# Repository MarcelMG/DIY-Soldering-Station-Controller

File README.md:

# DIY-Soldering-Station-Controller
A soldering station controller compatible with [Weller RT active tips](https://www.weller-tools.com/professional/USA/us/Professional/Soldering+technology/Soldering+tips+_+nozzles/Soldering+tips/RT+Active+Tips)
The design is kept simple, with a rotary encoder with internal pushbutton to set the temperature and
a TM1637 4-digit 7-segment LED display. When the pushbutton is pressed for >3s, the current target temperature is stored as default value in the non-volatile EEPROM memory of the microcontroller. When the iron handle is put in the stand, the iron goes into standby mode and reduces it's temperature to 100°C. Originally I planned to use a hall sensor to detect the handle in the stand, but I chose a simpler solution by connencting an input pin of the microcontroller with internal pullup resistor to the stand. Since the metal part of the iron tip is grounded, it can sets the pin low and thus enables to detect the iron in the stand.

The microcontroller used is a Microchip ATTiny24A. The program code just fits barely into the small flash memory (2kB), so a variant like the ATtiny44 (4kB) or 88 (8kB) might be more appropriate. The display is a TM1637 4-digit 7-segment LED display module, those can be found cheaply on ebay etc. One big advantage of these modules is, that they need only 2 GPIO pins to communicate with the display using an I²C-ish interface. The rotary encoder used has an internal pushbutton, the one I used is salvaged from an old radio. The power supply is a also salvaged from an old laptop or similar, it supplies 12V DC at something around 3.6A. The Weller RT tips are rated at 44W max., so a quite beefy power supply is needed. The Weller RT tips use a standard 3,5mm stereo audio jack connector with the following pinout:
* tip = heating element
* middle ring = thermocouple sensor
* sleeve (back ring) = GND

The thermocouple signal is amplified with a low input offset voltage rail-to-rail OpAmp and fed to the microcontrollers internal ADC. The µC's internal bandgap voltage reference is used. Two RC-lowpass filters in the signal path remove noise in the signal. It is important to only measure the thermocouple sensor voltage when the heating element is off, or else erroneous readings will be produced. To achieve this, the heater is controlled with a center-aligned (a.k.a. phase correct) PWM. In the middle of the low-cycle of the PWM, an interrupt triggers an AD-conversion. The PWM duty-cycle is computed with a P-controller to control the temperature. The heating element is switched with a p-MOSFET power transistor. To drive it's gate with 12V from the microcontrollers 5V level, another small nMOSFET is used. A PCB for the design has been designed and manufactured. The microcontroller is programmed via an 6-pin ISP connector.

This is the connection diagram (pinout) of the PCB:

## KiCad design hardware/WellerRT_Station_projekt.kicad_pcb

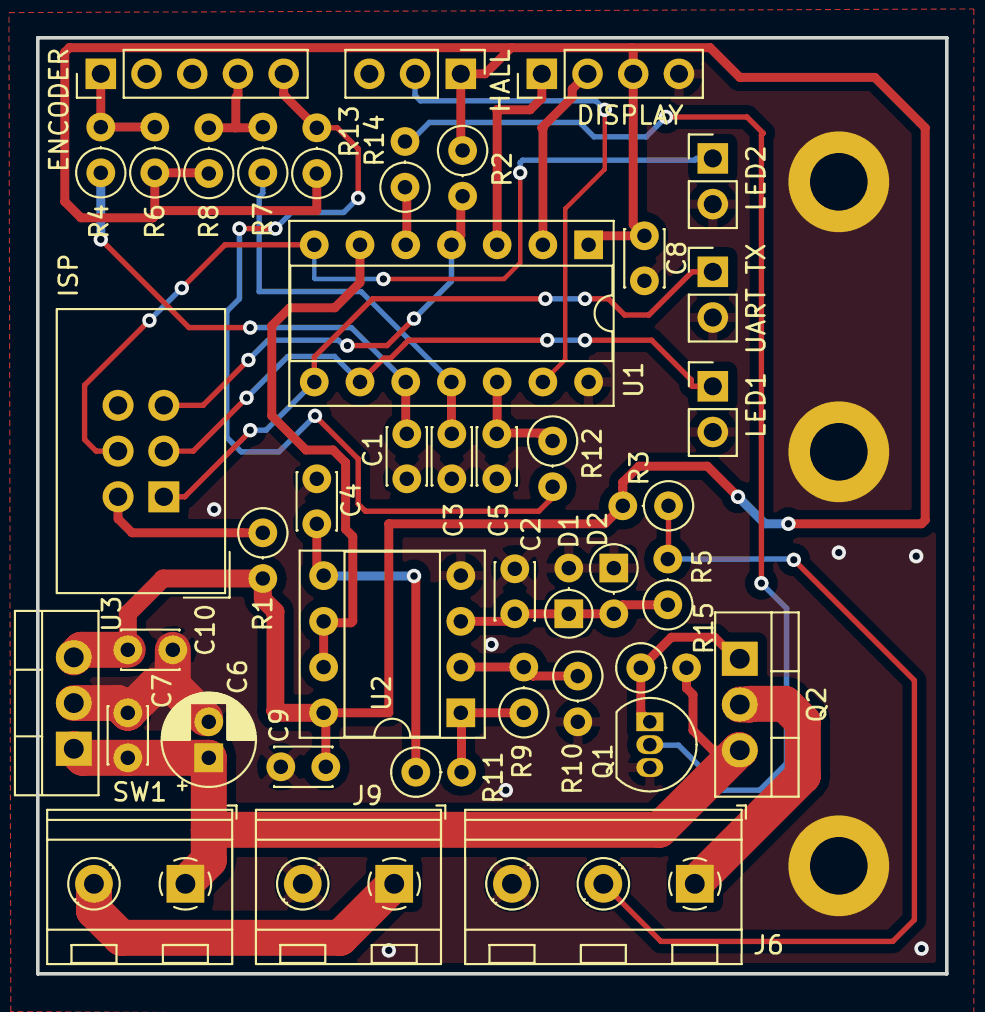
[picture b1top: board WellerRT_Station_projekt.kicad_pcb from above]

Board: 2 copper layers, 50.5 x 52.0 mm, 45 parts (0 on the bottom side), 28 nets.

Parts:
 ~: MountingHole_3.2mm_M3_DIN965_Pad
 ~#2,  ~#3: MountingHole_3.2mm_M3_DIN965_Pad
C1, C2, C3, C4, C5: 10n; C_Disc_D3.0mm_W2.0mm_P2.50mm
C6: 100µ; CP_Radial_D5.0mm_P2.00mm
C7: 330n; C_Disc_D3.0mm_W2.0mm_P2.50mm
C8, C9, C10: 100n; C_Disc_D3.0mm_W2.0mm_P2.50mm
D1, D2: D; D_DO-35_SOD27_P2.54mm_Vertical_AnodeUp
DISPLAY: TM1637_Display; PinHeader_1x04_P2.54mm_Vertical
ENCODER: Drehencoder; PinHeader_1x05_P2.54mm_Vertical
HALL: Halterung_Detektion; PinHeader_1x03_P2.54mm_Vertical
ISP: AVR-ISP-6; IDC-Header_2x03_P2.54mm_Vertical
J6: Weller RT Loetspitze; TerminalBlock_RND_205-00233_1x03_P5.08mm_Horizontal
J9: Netzteil; TerminalBlock_RND_205-00232_1x02_P5.08mm_Horizontal
LED1: LED1; PinHeader_1x02_P2.54mm_Vertical
LED2: LED2; PinHeader_1x02_P2.54mm_Vertical
Q1: BS170; TO-92_Inline
Q2: IRF4905; TO-220-3_Vertical
R1: 10; R_Axial_DIN0207_L6.3mm_D2.5mm_P2.54mm_Vertical
R2, R4, R6, R7, R8, R12, R13: 10k; R_Axial_DIN0207_L6.3mm_D2.5mm_P2.54mm_Vertical
R3: 1M; R_Axial_DIN0207_L6.3mm_D2.5mm_P2.54mm_Vertical
R5: 5.6k; R_Axial_DIN0207_L6.3mm_D2.5mm_P2.54mm_Vertical
R9, R11: 100k; R_Axial_DIN0207_L6.3mm_D2.5mm_P2.54mm_Vertical
R10, R15: 1k; R_Axial_DIN0207_L6.3mm_D2.5mm_P2.54mm_Vertical
R14: 220; R_Axial_DIN0207_L6.3mm_D2.5mm_P2.54mm_Vertical
SW1: SW_SPST; TerminalBlock_RND_205-00232_1x02_P5.08mm_Horizontal
U1: ATtiny24A-PU; DIP-14_W7.62mm_Socket
U2: MCP607; DIP-8_W7.62mm_Socket
U3: L7805; TO-220-3_Vertical
UART TX: UART_TX; PinHeader_1x02_P2.54mm_Vertical

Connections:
+5V: C8.1, C9.1, C10.1, DISPLAY.3, HALL.1, R1.2, R2.1, R3.2, R6.1, R8.1, R13.1, U1.1, U2.8, U3.3
+12V: C6.1, C7.1, Q2.3, R15.2, SW1.1, U3.1
ENCODER_A: ENCODER.4, R7.2, R8.2
ENCODER_B: ENCODER.5, R12.2, R13.2
GND: ~.1, ~#2.1, ~#3.1, C1.2, C2.1, C3.2, C4.1, C5.2, C6.2, C7.2, C8.2, C9.2, C10.2, D1.2, D2.1, DISPLAY.4, ENCODER.2, ENCODER.3, HALL.3, ISP.6, J6.3, J9.2, LED1.2, LED2.2, Q1.3, R10.2, U1.14, U2.4, U3.2, UART TX.2
HEIZELEMENT: J6.1, Q2.2
unnamed: C2.2, D1.1, D2.2, R5.1, U2.3
unnamed: C4.2, R11.1, U2.5
unnamed: ISP.2, R1.1
unnamed: J9.1, SW1.2
unnamed: Q1.1, Q2.1, R15.1
unnamed: Q1.2, R14.2
unnamed: R9.2, R10.1, U2.2
unnamed: R9.1, R11.2, U2.1
PA0: HALL.2, U1.13
PA1: C5.1, R12.1, U1.12
PA2: C3.1, R7.1, U1.11
PA3: C1.1, R4.1, U1.10
PA4: ISP.3, LED1.1, U1.9
PA5: ISP.1, U1.8, UART TX.1
PA6: ISP.4, LED2.1, U1.7
PA7: U1.6, U2.6, U2.7
PB2: R14.1, U1.5
RESET: ISP.5, R2.2, U1.4
TASTER: ENCODER.1, R4.2, R6.2
THERMOFUEHLER: J6.2, R3.1, R5.2
TM1637_CLK: DISPLAY.1, U1.3
TM1637_DIO: DISPLAY.2, U1.2

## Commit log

2019-12-26 initial upload
